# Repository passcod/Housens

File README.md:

# Housens

Project to make my own low-power house sensors.

Current iteration (r002):

- Bluetooth
- ambient light (OPT3005)
- pressure, humidity, temperature (BME280)
- carbon dioxide (STCC4)
- STM32WB core
- powered from CR2032
- 50x50mm

Hardware licensed [CERN-OHL-S](https://ohwr.org/project/cernohl/-/wikis/uploads/b236492596cfc91c12def7d50bbf7da0/cern_ohl_s_v2.pdf).

Firmware licensed [GPL-3.0-or-later](https://opensource.org/license/gpl-3-0).

## Renders

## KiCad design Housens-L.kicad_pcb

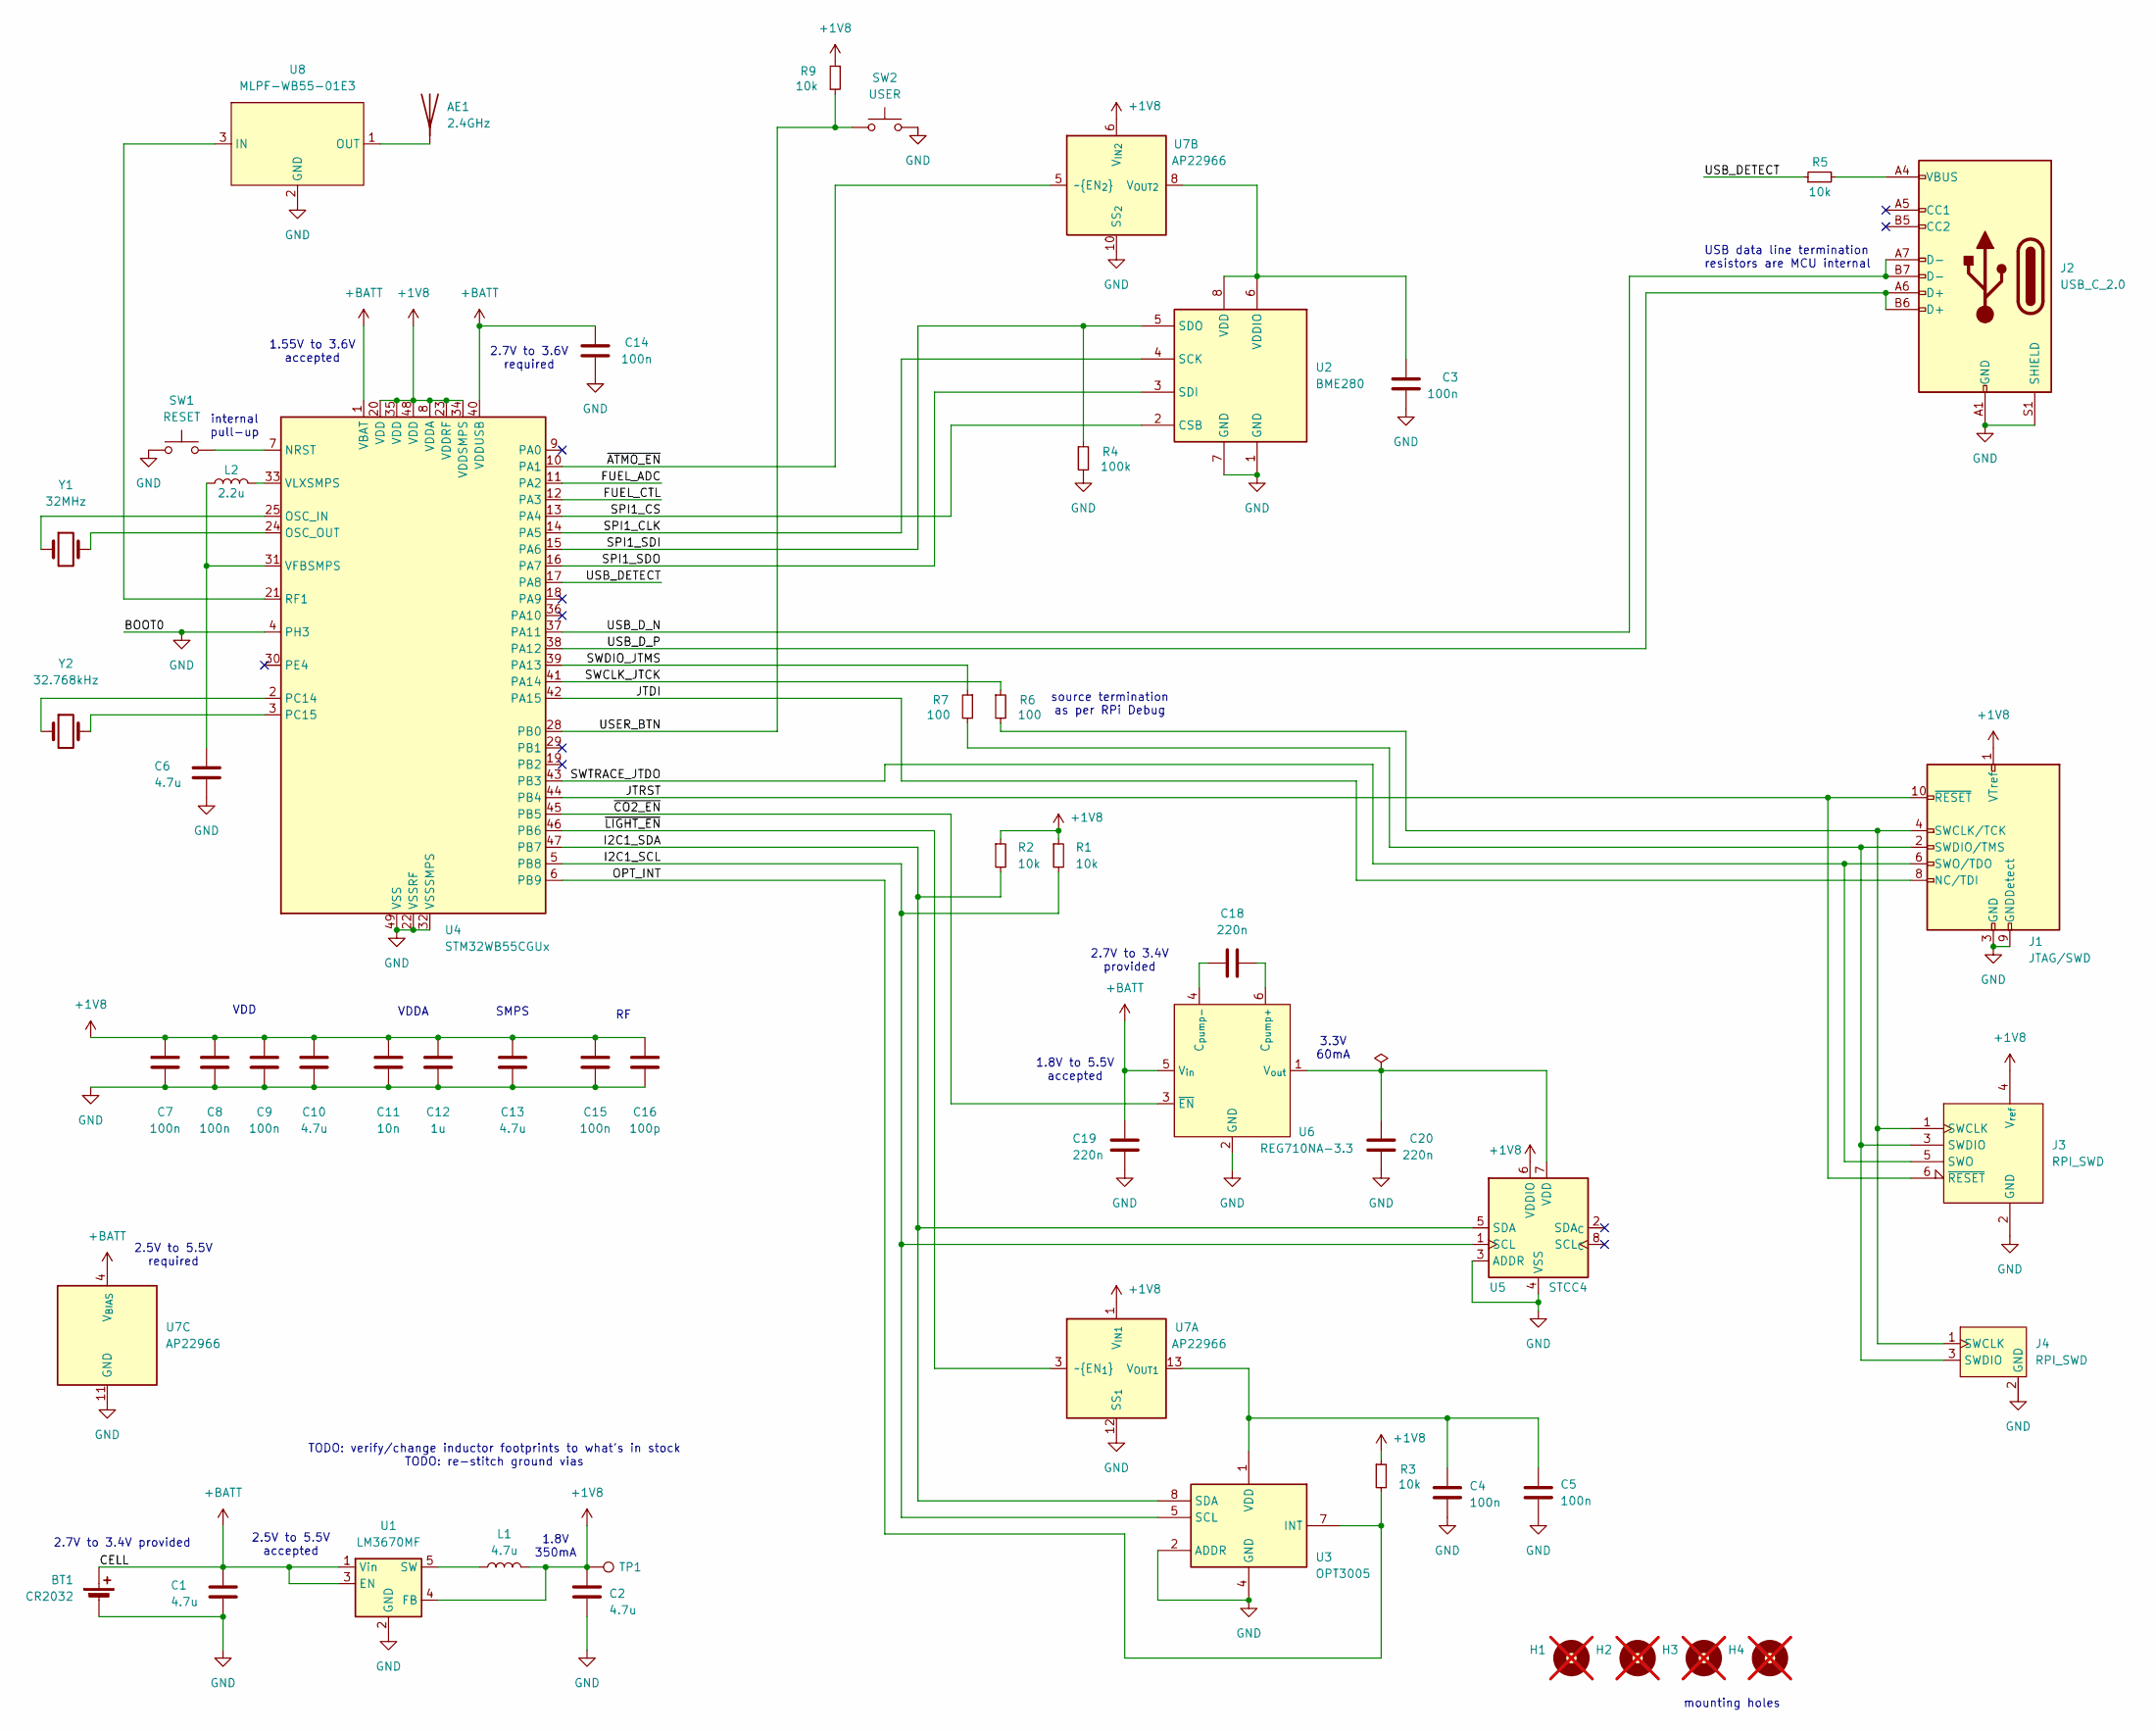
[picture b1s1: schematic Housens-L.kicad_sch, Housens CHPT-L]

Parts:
AE1: 2.4GHz; Texas_SWRA117D_2.4GHz_Right_BigHole
BT1: CR2032; SolderWire-0.1sqmm_1x02_P3.6mm_D0.4mm_OD1mm_Relief
C1, C2, C6, C10, C13: 4.7u; C_0603_1608Metric
C3, C4, C5, C7, C8, C9, C14, C15: 100n; C_0603_1608Metric
C11: 10n; C_0603_1608Metric
C12: 1u; C_0603_1608Metric
C16: 100p; C_0603_1608Metric
C18, C19, C20: 220n; C_0603_1608Metric
H1, H2, H3, H4: MountingHole_M3; MountingHole_3.2mm_M3; not fitted
J1: JTAG/SWD; PinHeader_2x05_P1.27mm_Vertical_SMD
J2: USB_C_2.0; USB_C_Receptacle_GCT_USB4085
J3: RPI_SWD; Tag-Connect_TC2030-IDC-NL_2x03_P1.27mm_Vertical
J4: RPI_SWD; JST_SH_SM03B-SRSS-TB_1x03-1MP_P1.00mm_Horizontal
L1: 4.7u; L_Wuerth_WE-TPC-2811
L2: 2.2u; L_Wuerth_WE-TPC-2811
R1, R2, R3, R5, R9: 10k; R_0603_1608Metric
R4: 100k; R_0603_1608Metric
R6, R7: 100; R_0603_1608Metric
SW1: RESET; SW_PUSH_6mm
SW2: USER; SW_PUSH_6mm
TP1: TestPoint; TestPoint_Pad_D2.0mm
U1: LM3670MF; TSOT-23-5; Part LM3670MFX-1.8/NOPB
U2: BME280; Bosch_LGA-8_2.5x2.5mm_P0.65mm_ClockwisePinNumbering
U3: OPT3005; OPT3005DTSR; Manufacturer_Part_Number OPT3005DTSR; Mouser Part Number 595-OPT3005DTSR
U4: STM32WB55CGUx; QFN-48-1EP_7x7mm_P0.5mm_EP3.5x3.5mm
U5: STCC4
U6: REG710NA-3.3; SOT-23-6
U7: AP22966; DFN-14-1EP_3x2mm_P0.4mm_EP1.78x1.35mm_AP22966
U8: MLPF-WB55-01E3
Y1: 32MHz; Crystal_C38-LF_D3.0mm_L8.0mm_Horizontal
Y2: 32.768kHz; Crystal_C38-LF_D3.0mm_L8.0mm_Horizontal

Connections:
+1V8: C2.1, C7.1, C8.1, C9.1, C10.1, C11.1, C12.1, C13.1, C15.1, C16.1, J1.1 (VTref), J3.4 (V_{ref}), L1.2, R1.1, R2.1, R3.1, R9.1, TP1.1, U1.4 (FB), U4.8 (VDDA), U4.20 (VDD), U4.23 (VDDRF), U4.34 (VDDSMPS), U4.35 (VDD), U4.48 (VDD), U5.6 (VDDIO), U7.1 (V_{IN1}), U7.2 (V_{IN1}), U7.6 (V_{IN2}), U7.7 (V_{IN2})
+BATT: BT1.1 (+), C1.1, C14.1, C19.1, U1.1 (Vin), U1.3 (EN), U4.1 (VBAT), U4.40 (VDDUSB), U6.5 (V_{in}), U7.4 (V_{BIAS})
/FUEL_ADC: U4.11 (PA2)
/FUEL_CTL: U4.12 (PA3)
/I2C1_SCL: R1.2, U3.5 (SCL), U4.5 (PB8), U5.1 (SCL)
/I2C1_SDA: R2.2, U3.8 (SDA), U4.47 (PB7), U5.5 (SDA)
/JTDI: J1.8 (NC/TDI), U4.42 (PA15)
/JTRST: J1.10 (~RESET), J3.6 (~RESET), U4.44 (PB4)
/OPT_INT: R3.2, U3.7 (INT), U4.6 (PB9)
/SPI1_CLK: U2.4 (SCK), U4.14 (PA5)
/SPI1_CS: U2.2 (CSB), U4.13 (PA4)
/SPI1_SDI: R4.1, U2.5 (SDO), U4.15 (PA6)
/SPI1_SDO: U2.3 (SDI), U4.16 (PA7)
/SWCLK_JTCK: R6.1, U4.41 (PA14)
/SWDIO_JTMS: R7.1, U4.39 (PA13)
/SWTRACE_JTDO: J1.6 (SWO/TDO), J3.5 (SWO), U4.43 (PB3)
/USB_DETECT: R5.1, U4.17 (PA8)
/USB_D_N: J2.A7 (D-), J2.B7 (D-), U4.37 (PA11)
/USB_D_P: J2.A6 (D+), J2.B6 (D+), U4.38 (PA12)
/USER_BTN: R9.2, SW2.2, U4.28 (PB0)
/~ATMO_EN: U4.10 (PA1), U7.5 (~EN_{2})
/~CO2_EN: U4.45 (PB5), U6.3 (~EN)
/~LIGHT_EN: U4.46 (PB6), U7.3 (~EN_{1})
GND: BT1.2 (-), C1.2, C2.2, C3.2, C4.2, C5.2, C6.2, C7.2, C8.2, C9.2, C10.2, C11.2, C12.2, C13.2, C14.2, C15.2, C16.2, C19.2, C20.2, J1.3 (GND), J1.5 (GND), J1.9 (GNDDetect), J2.A1 (GND), J2.A12 (GND), J2.B1 (GND), J2.B12 (GND), J2.S1 (SHIELD), J3.2 (GND), J4.2 (GND), R4.2, SW1.1, SW2.1, U1.2 (GND), U2.1 (GND), U2.7 (GND), U3.2 (ADDR), U3.4 (GND), U4.4 (PH3), U4.22 (VSSRF), U4.32 (VSSSMPS), U4.49 (VSS), U5.3 (ADDR), U5.4 (VSS), U6.2 (GND), U7.10 (SS_{2}), U7.11 (GND), U7.12 (SS_{1}), U7.15 (GND), U8.2 (GND), U8.4 (GND), U8.5 (GND), U8.6 (GND)
unnamed: AE1.1 (A), U8.1 (OUT)
unnamed: J1.4 (SWCLK/TCK), J3.1 (SWCLK), J4.1 (SWCLK), R6.2
unnamed: J1.2 (SWDIO/TMS), J3.3 (SWDIO), J4.3 (SWDIO), R7.2
unnamed: J2.A4 (VBUS), J2.A9 (VBUS), J2.B4 (VBUS), J2.B9 (VBUS), R5.2
unnamed: L1.1, U1.5 (SW)
unnamed: C3.1, U2.6 (VDDIO), U2.8 (VDD), U7.8 (V_{OUT2}), U7.9 (V_{OUT2})
unnamed: C4.1, C5.1, U3.1 (VDD), U7.13 (V_{OUT1}), U7.14 (V_{OUT1})
unnamed: SW1.2, U4.7 (NRST)
unnamed: U4.25 (OSC_IN), Y1.1
unnamed: U4.24 (OSC_OUT), Y1.2
unnamed: U4.2 (PC14), Y2.1
unnamed: U4.3 (PC15), Y2.2
unnamed: U4.21 (RF1), U8.3 (IN)
unnamed: C6.1, L2.1, U4.31 (VFBSMPS)
unnamed: L2.2, U4.33 (VLXSMPS)
unnamed: C20.1, U5.7 (VDD), U6.1 (V_{out})
unnamed: C18.2, U6.6 (C_{pump+})
unnamed: C18.1, U6.4 (C_{pump-})

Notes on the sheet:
SMPS
1.8V to 5.5V accepted
2.7V to 3.6V required
2.5V to 5.5V accepted
3.3V 60mA
2.7V to 3.4V provided
internal pull-up
2.7V to 3.4V provided
TODO: verify/change inductor footprints to what's in stock TODO: re-stitch ground vias
1.8V 350mA
source termination as per RPi Debug
mounting holes
USB data line termination resistors are MCU internal
2.5V to 5.5V required
VDDA
VDD
1.55V to 3.6V accepted

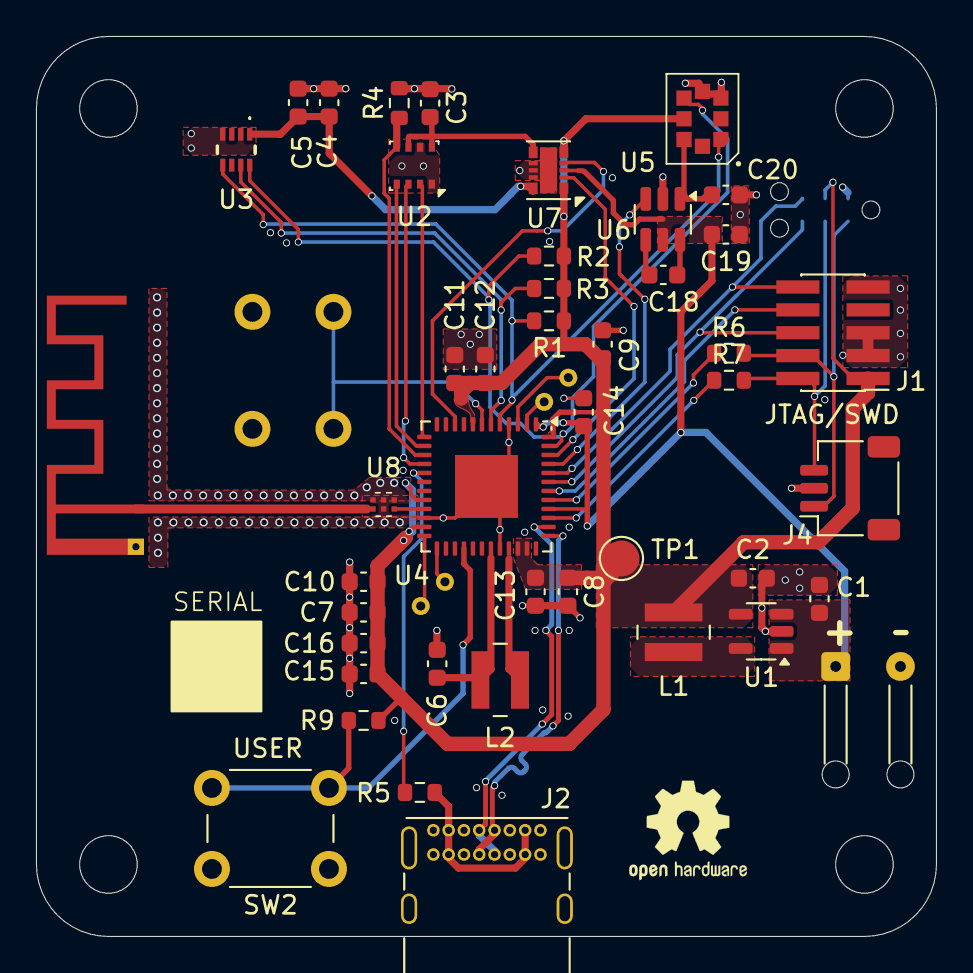
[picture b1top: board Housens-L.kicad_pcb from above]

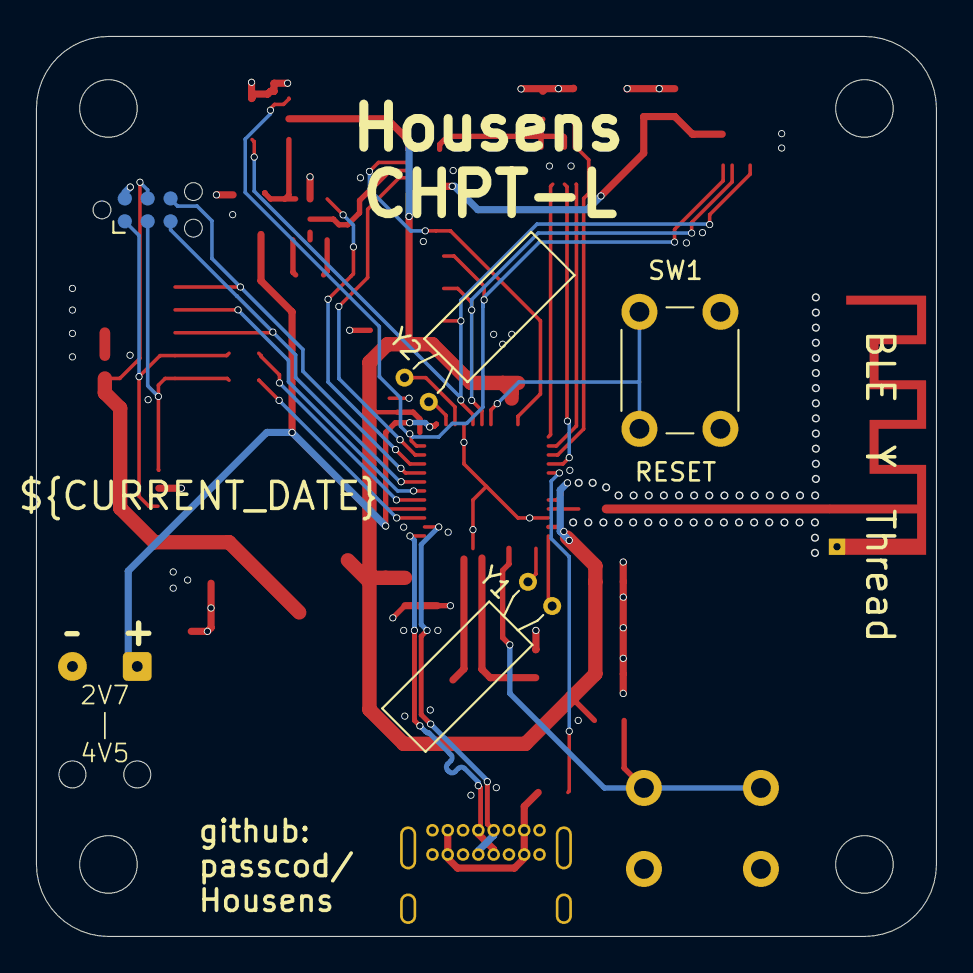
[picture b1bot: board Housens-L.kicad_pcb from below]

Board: 4 copper layers, 50.0 x 50.0 mm, 52 parts (4 on the bottom side), 40 nets.

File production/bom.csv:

Designator,Footprint,Quantity,Value,LCSC Part #
AE1,Texas_SWRA117D_2.4GHz_Right_BigHole,1,2.4GHz,
BT1,BAT-HLD-001_2Pins,1,CR2032,
"C1, C10, C13, C2, C6",0603,5,4.7u,
C11,0603,1,10n,
C12,0603,1,1u,
"C14, C15, C3, C4, C5, C7, C8, C9",0603,8,100n,
C16,0603,1,100p,
"C18, C19, C20",0603,3,220n,
J1,PinHeader_2x05_P1.27mm_Vertical_SMD,1,JTAG/SWD,
J2,USB_C_Receptacle_GCT_USB4085,1,USB_C_2.0,
J4,JST_SH_SM03B-SRSS-TB_1x03-1MP_P1.00mm_Horizontal,1,RPI_SWD,
L1,L_Wuerth_WE-TPC-2811,1,4.7u,
L2,L_Wuerth_WE-TPC-2811,1,2.2u,
"R1, R2, R3, R5, R9",0603,5,10k,
R4,0603,1,100k,
"R6, R7",0603,2,100,
SW1,SW_PUSH_6mm,1,RESET,
SW2,SW_PUSH_6mm,1,USER,
TP1,TestPoint_Pad_D2.0mm,1,TestPoint,
U1,TSOT-23-5,1,LM3670MF,
U2,Bosch_LGA-8_2.5x2.5mm_P0.65mm_ClockwisePinNumbering,1,BME280,
U3,OPT3005DTSR,1,OPT3005,
U4,QFN-48-1EP_7x7mm_P0.5mm_EP5.6x5.6mm_ThermalVias_OneSided,1,STM32WB55CGUx,
U5,STCC4-PROVISIONAL,1,STCC4,
U6,SOT-23-6,1,REG710NA-3.3,
U7,DFN-14-1EP_3x2mm_P0.4mm_EP1.78x1.35mm_AP22966,1,AP22966,
U8,MLPF-WB55-01E3,1,MLPF-WB55-01E3,
Y1,Crystal_SMD_2016-4Pin_2.0x1.6mm,1,32MHz,
Y2,Crystal_AT310_D3.0mm_L10.0mm_Horizontal,1,32.768kHz,

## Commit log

2025-01-25 Initial project libraries
2025-01-25 Add component list
2025-01-25 Add power supply
2025-01-25 Add sensors
2025-01-25 Add MCU
2025-01-25 Add battery
2025-01-25 Add debug connector
2025-01-25 Add USB connector
2025-01-25 Layout board edge
2025-01-25 Initial spatial layout
2025-01-25 Graphics
2025-01-25 Add OPT3005 model
2025-01-25 Layout power supply
2025-01-25 Add TODO about touchsense
2025-01-26 Layout antenna
2025-01-26 Add fuel gauge
2025-01-26 Custom thermal footprint for MCU
2025-01-26 Layout 1V8 and USB
2025-01-26 Add missing 3D models
2025-01-26 Layout JTAG
2025-01-26 Add 3D model for cell holder
2025-01-26 Show some labels
2025-01-26 Layout BME280
2025-01-26 Layout I2C
2025-01-26 Layout SPI
2025-01-26 Impedance-match USB lines
2025-01-26 Stitch and finalise labels
2025-01-26 Generate production files
2025-01-26 Replace crystals
2025-01-26 Run DRC
2025-01-26 Replace vias with the cheap ones
2025-01-26 Add datasheet for buttons
2025-01-27 Fix hole sizes
2025-01-27 More hole size fixes
2025-01-27 Add license
2025-01-27 Rename
2025-01-28 Fix 3D view
2025-01-29 Remove external fuel measurement as MCU has one built in
2025-01-29 Add power control to peripherals
2025-01-29 Add provisional STCC4 sensor
2025-01-29 Add note on upcoming sensor
2025-01-30 Add power supply for SCCT4 and dual fets for others
2025-01-30 Layout for recent changes
2025-01-30 Add renders
2025-01-30 Relayout debug port
2025-01-30 According to TI, the antenna via should go to ground
2025-02-03 Use proper load switch instead of plain FET
2025-02-03 Fix core name
2025-02-03 Add matching circuit to antenna
2025-02-03 Space out the sensors
2025-02-03 Replace matching circuit with IPD
    This is more compact, purpose-made, and cheaper than the individual components!
2025-02-04 Replace supply with LM3671MF as MCP1603 is not stocked
2025-02-06 add connector part no
2025-02-06 Use LM voltage reg instead of unobtainium MCP
2025-02-07 Add RPi-style debug port
2025-02-07 Make STCC4 silk prettier
2025-02-07 Update production files
2025-02-08 Restitch at 1/20th wavelength
2025-02-09 relicense hardware
2025-05-06 updates from sourcing hardware
2025-06-22 Replace soldered CR battery holder with wire connections
    - it liberates a large amount of board space
    - soldering this thing was really annoying to do by hand
    - a significant problem turns out to be that in high-condensation environment
    (e.g. outside) the battery drains itself via conduction through the humidity
    on the cell, reducing battery life from months to days. being able to seal
    the battery separately from the sensors / rest of the board is an advantage.
2025-06-24 Use released STCC4 details
